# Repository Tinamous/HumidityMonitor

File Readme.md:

3D Printer Filament Humidity Controlled Storage
===============================================

Comprises of:

* Outer box (19L XL Really Useful Box).
* Laser cut acrylic silica gel case
* Particle Photon based humidity sensing and fan control PCB inside silica gel case.
* Self indicating silica gel inside #2.

1) Outer box
---------------------
A 19L XL A4 suspension folder Really Useful Box works well. Be sure to get the one with the high lid. (not the regular 19L box).

* Needed: Staples link to case.
* Maplin: http://www.maplin.co.uk/p/really-useful-19l-xl-box-n68fl (Untested but it's a lot cheaper than the staples one!)

The lid of the 19L XL case will need to be drilled to hold the acrylic silica gel cartridge in place. Do this before gluing the cartridge so the acrylic can be used as a template.

Place what is labeled as the top piece in the designs (actually the bottom piece with all the holes in it) onto the lid and mark/drill the 4 corner screws.

If you wish for the power to go in via the top (prevents boxes being stacked but is obvious that it is powered so prevents people missing it) use the large bottom piece (actually top) with the larger round hole in it and align the two corner screws then drill out the larger hole in the lid.

Power connectors were sourced from eBay (http://www.ebay.co.uk/itm/PLUGZ2GO-2-1MM-X-5-5MM-PANEL-MOUNT-DC-PLUG-SOCKET-JACK-CHOICE-OF-COLOUR-/221456273750?var=&hash=item338fd29156:m:m85llLg3q2OnjM6yf-dwyPw), be sure you can get the same before drilling the power connector hole in the lid. 

Alternativly power connection may be done from the side of the lid by running the power cable out of either top or bottom gel case holes, this would allow the boxes to be stacked, although it makes it less obvious theirs a cable connected so care needs to be taken.

M4 x 70mm machine screws with washer+wingnut on the lit are used to hold the actylic case to the lid. (See notes below on re-filling the silica gel)

2) Laser Cut Acrylic Gel Case
-----------------------------
5mm clear acrylic cut as detailed in Hardware\Case\LaserCut

(You can use another colour obviously but the clear is cheaper and allows the self indicating gel to be seen).

The case contains a 40mm fan. A standard 3 pin PC fan should be used with a filter to prevent silica gel getting in to it.

3) Humidity Monitor.
---------------------

Use Particle Photon (or can use Particle Core device).

See Hardware\PCB\V2

Don't use V1 as the FET has Source/Drain the wrong way around.

PCB available from OSHPark: https://oshpark.com/shared_projects/nOVDuNCE

JP3 or JP4 are used for the HTU21 sensor. SparkFun and eBay boards have swapped SDA/SCL, watch for correct version.
* JP3 is for the eBay version
* JP4 is for SparkFun version.

Build using build.particle.io, see source folder.

A 12V power supply us needed capable of supplying upto 500mA (depends on the fan).

If a 5V fan is used a 5V PSU can be used and the onboard regulator not fitted, instead connecting the Vin to VOut holes with a piece of wire.

The PCB is mounted to the case with 4x 10mm plastic standoffs and 8x M3x8mm bolts from either side.

4) Self indicating silica gel
-----------------------------
Almost any silica gel can be used and doesn't need to be self indicating but it helps with seeing when the gel needs to be dried and when drying the gel that it is ready.

Gel should be stored in a sealed box/bag when not in use.

Gel can be re-generated by heating in an electric (untested on gas) oven for about 3 hours at 110°C

5) Connection to Tinamous
-------------------------
Optional step. Tinamous supports Particle devices by use of the ParticleBot in Tinamous and will automatically bring in and store devices/measurements so the humidity can be remotely monitored.

PLA Filament storage 24 hour humdity chart:

PLA Filament storage 7 day humidity chart with change of gel:

Notes
=====

Replacing the silica gel.
--------------------------

This needs to be done regularly (depending on usage), ca. every month and the silica gel dried (110C 3hrs spread out on a baking tray). I typically replace when it gets to about 20% humidity in the box.

The silica gel can be dried and re-used.

Silica gel will try to go everywhere.

* Remove acrylic case from box lid (place on flat surface, undo wing nuts on top of box.
* Remove lid upwards leaving acrylic case on flat surface.
* Replace 2x win nuts onto acrylic case at PCB end to hold the large top piece in place
* Remove small top piece from top to expose silica gel
* Remove 2x screws that were holding the top peice in
** failure to remove these now will result in silica gel getting wedged behind them and stopping correct alignment.
* Pour gel into a container (suggest Sistem 2.35L tub - http://www.amazon.co.uk/gp/product/B005D6Y4IA?psc=1&redirect=true&ref_=oh_aui_detailpage_o03_s00)
* Put funnel into opening
* Slowly pour fresh silica gel into acrylic case, shaking to move the gel down the case as you go
* Do not fill completly full, allow 1/2-1 inch space when the case is closed up and stood tall 
* Re-Fit small lid peiece
* Holding top in place, stand case tall to allow silica gel to fully move down to the fan and make re-fitting screws easier.
* Refit 2x screws for the small lid piece.
* Stand back down, remove 2x wingnuts to allow lit to be fitted.
* Fit box lit and re-fit wing nuts.

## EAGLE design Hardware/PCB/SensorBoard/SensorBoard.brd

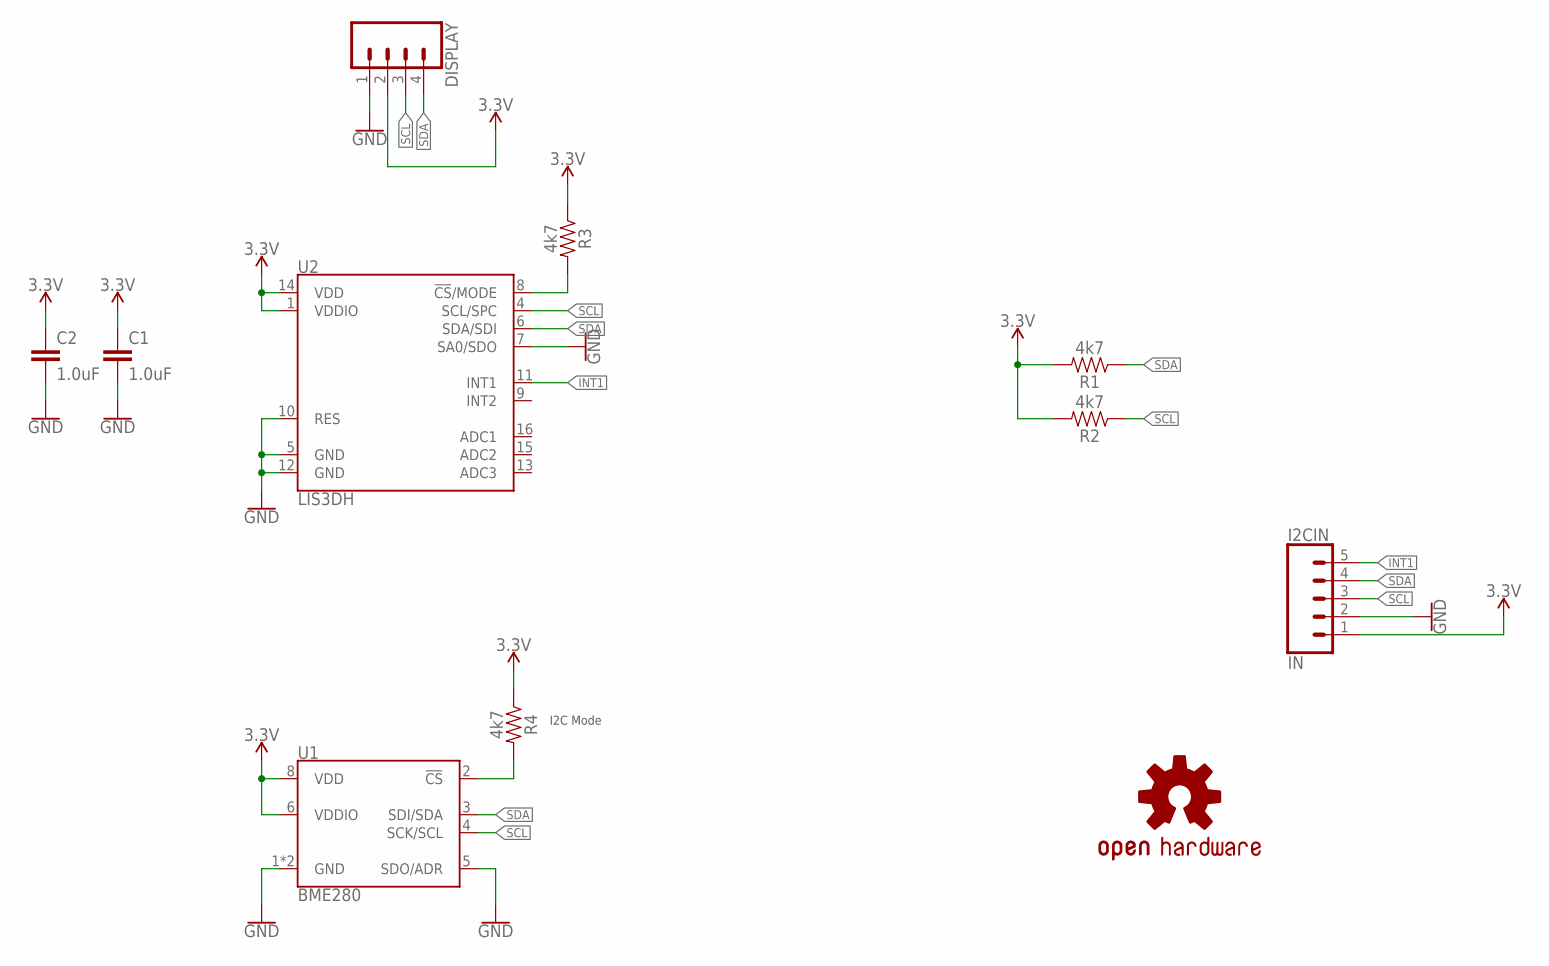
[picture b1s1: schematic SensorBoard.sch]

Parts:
C1, C2: 1.0uF; 0805
DISPLAY: CONN_04; 1X04
I2CIN: IN; 1X05
LOGO1: OSHW-LOGOL; OSHW-LOGO-L
R1, R2, R3, R4: 4k7; 0805
U1: BME280; LGA-8-2.5X2.5
U2: LIS3DH; LGA-16-3X3

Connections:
3.3V: C1.1, C2.1, DISPLAY.2, I2CIN.1, R1.2, R2.2, R3.1, R4.1, U1.6 (VDDIO), U1.8 (VDD), U2.1 (VDDIO), U2.14 (VDD)
GND: C1.2, C2.2, DISPLAY.1, I2CIN.2, U1.1 (GND), U1.5 (SDO/ADR), U1.7 (GND), U2.5 (GND), U2.7 (SA0/SDO), U2.10 (RES), U2.12 (GND)
INT1: I2CIN.5, U2.11 (INT1)
unnamed: R4.2, U1.2 (!CS)
unnamed: R3.2, U2.8 (!CS!/MODE)
SCL: DISPLAY.3, I2CIN.3, R2.1, U1.4 (SCK/SCL), U2.4 (SCL/SPC)
SDA: DISPLAY.4, I2CIN.4, R1.1, U1.3 (SDI/SDA), U2.6 (SDA/SDI)

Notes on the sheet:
I2C Mode

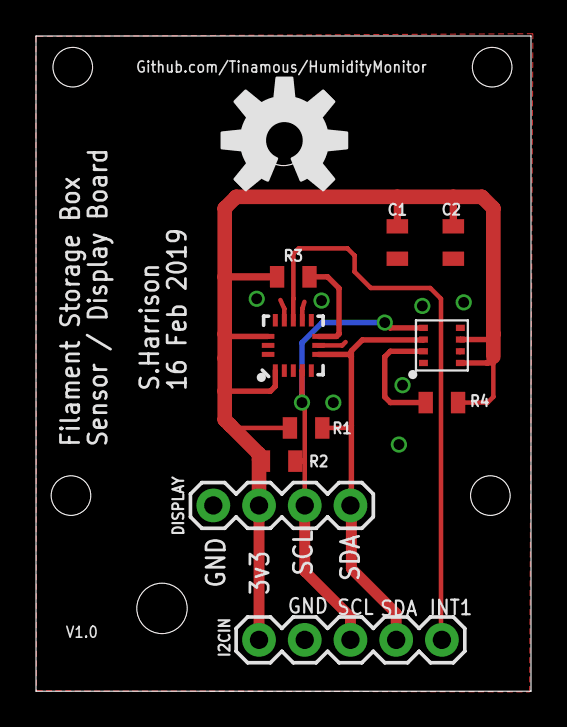
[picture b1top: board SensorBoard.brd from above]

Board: 2 copper layers, 27.5 x 36.4 mm, 11 parts (0 on the bottom side), 7 nets.

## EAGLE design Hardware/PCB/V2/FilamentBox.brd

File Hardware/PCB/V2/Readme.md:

Filament Box IoT Humidity Sense and Control
---------------------------------------------

Used to monitor the humidity level in a 3D filament storage box and re-circulate the air through a silica gel cartridge.

Notes:
* 7805 Regulator should be replaces with a switching "780x replacement" type device to keep heat down. The 7805 will get very hot dropping 12v to 5v.
* JP3 and 4 are variants of connectors for HTU21D breakout boards.
** JP4 should be used with the Spark Fun version (https://www.sparkfun.com/products/12064)
** JP3 should be used with the common eBay version (SDA/SCL swapped from Spark Fun version).
* Normal use is intended for 12V with a 12V fan. However if using a 5V fan the supply may be dropped to 5V and IC1 (7805) not fitted, instead pads 1 & 3 connected to feed 5V directly into the photo's 5V supply pin.
* Do not use photon USB B connector to provide 5V for fan, it will not supply the full 5v and may not have PCB traces strong enough for the fan current.

Untested at this time. Awaiting PCBs.

BOM:

All 0805 unless specified

F1 - Fuse Farnell 1822224

D1,D2 - IN4148W (2x)
D4 - MBRA140
D3 - Green Reverse LED
D7 - Red Reverse LED
D8 - Yellow Reverse LED

R1,R2 - 10k (2x)
R3 - 100k
R4 - 180R
R5,R6,R7 - 1k5 (3x)

Q1 - BC817
Q2 - NXP2301

C1 - 1.0uF 
C4 - 0.1 25V
C2,C5 - 0.1uF (x)

SG1 - Buzzer (Farnell: 2098836)

JP1 - 2 Pin Molex + Header + 2.1MM DC Jack 973-1148
JP2 - 3 Pin Moxel + 3 wire 40mm fan 9731156

IC1 - 7805 equivelant
JP3 - HTU21D equv
U3 - Photon (needs 2x 18Pin headers)

PCB Spacers (4x)
M3 Machine Screws (8x)

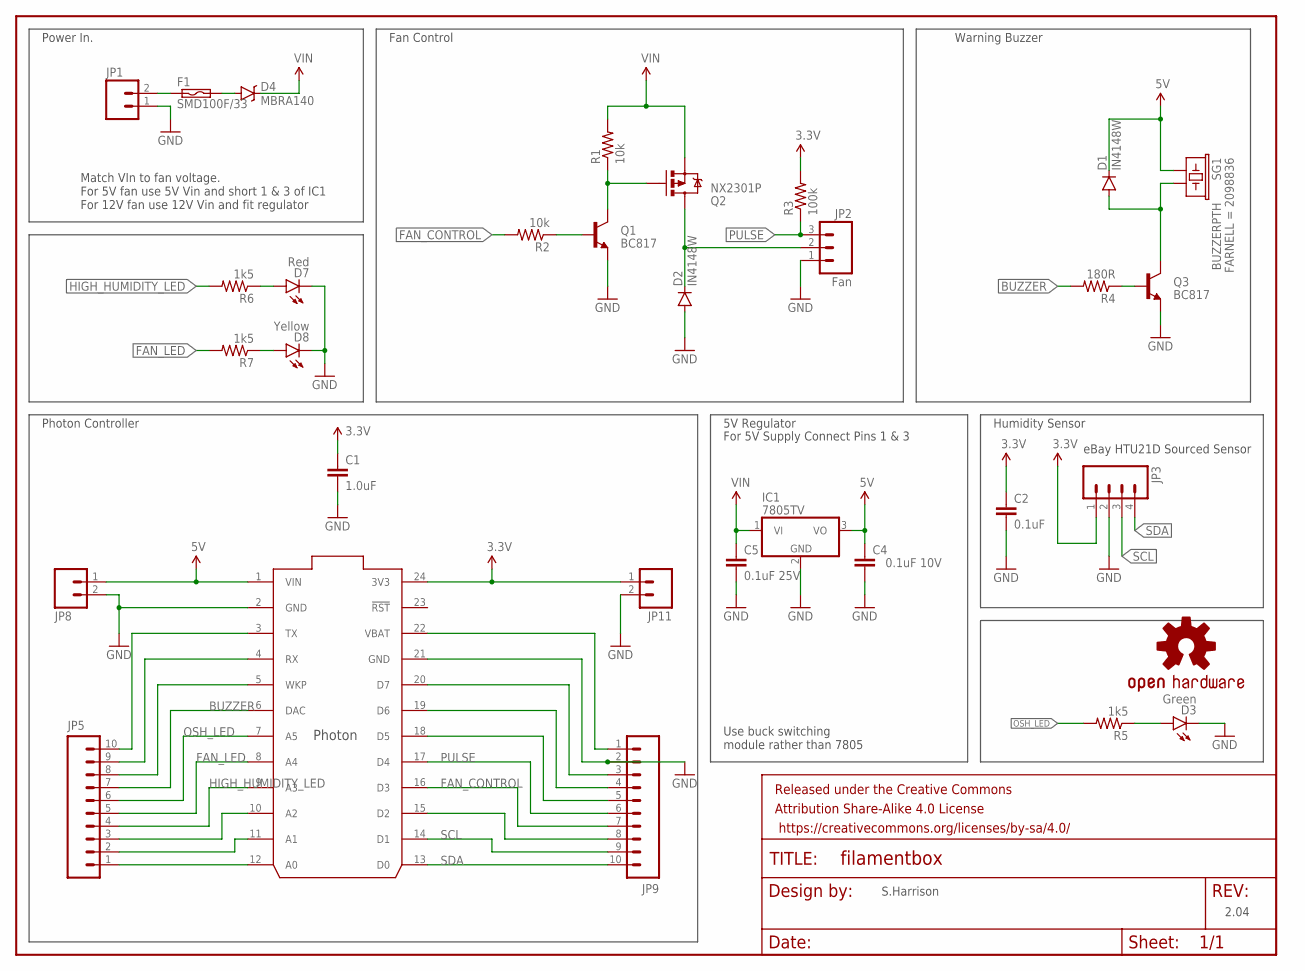
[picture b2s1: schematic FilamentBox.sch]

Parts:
C1: 1.0uF; 0805-CAP
C2: 0.1uF; 0805-CAP
C4: 0.1uF 10V; 0805-CAP
C5: 0.1uF 25V; 0805-CAP
D1, D2: IN4148W; SOD-123
D3: Green; LED-1206-BOTTOM
D4: MBRA140; SMA-DIODE
D7: Red; LED-1206-BOTTOM
D8: Yellow; LED-1206-BOTTOM
F1: SMD100F/33; SMD050F; MFGPART 2920L075DR; FARNELL 1822224
FRAME1: FRAME-LETTER; CREATIVE_COMMONS
IC1: 7805TV; TO220V
JP1: M02POLAR; MOLEX-1X2
JP2: Fan; MOLEX-1X3
JP3: M04PTH; 1X04
JP5, JP9: M10NO_SILK_PTH_FEMALE; 1X10_NO_SILK
JP8, JP11: M021X02_NO_SILK; 1X02_NO_SILK
LOGO1: OSHW-LOGOL; OSHW-LOGO-L
Q1, Q3: BC817; SOT23-BEC
Q2: NX2301P; SOT23-3
R1, R2: 10k; 0805
R3: 100k; 0805
R4: 180R; 0805
R5, R6, R7: 1k5; 0805
SG1: BUZZERPTH; BUZZER-12MM; FARNELL 2098836
U3: PHOTON

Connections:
3.3V: C1.1, C2.1, JP3.1, JP11.1, R3.2, U3.24 (3V3)
5V: C4.1, D1.C, IC1.3 (VO), JP8.1, SG1.+ (1), U3.1 (VIN)
BUZZER: JP5.7, R4.2, U3.6 (DAC)
FAN_CONTROL: JP9.7, R2.2, U3.16 (D3)
FAN_LED: JP5.5, R7.2, U3.8 (A4)
GND: C1.2, C2.2, C4.2, C5.2, D2.A, D3.C, D7.C, D8.C, IC1.2 (GND), JP1.1, JP2.1, JP3.2, JP8.2, JP9.2, JP11.2, Q1.E, Q3.E, U3.2 (GND), U3.21 (GND)
HIGH_HUMIDITY_LED: JP5.4, R6.2, U3.9 (A3)
unnamed: JP5.1, U3.12 (A0)
unnamed: Q1.C, Q2.1 (G), R1.1
unnamed: JP5.2, U3.11 (A1)
unnamed: Q1.B, R2.1
unnamed: JP5.3, U3.10 (A2)
unnamed: D2.C, JP2.2, Q2.3 (D)
unnamed: JP9.8, U3.15 (D2)
unnamed: JP5.8, U3.5 (WKP)
unnamed: JP5.9, U3.4 (RX)
unnamed: JP5.10, U3.3 (TX)
unnamed: Q3.B, R4.1
unnamed: D1.A, Q3.C, SG1.- (2)
unnamed: JP9.3, U3.20 (D7)
unnamed: JP9.1, U3.22 (VBAT)
unnamed: D3.A, R5.1
unnamed: F1.1, JP1.2
unnamed: D4.A, F1.2
unnamed: JP9.4, U3.19 (D6)
unnamed: JP9.5, U3.18 (D5)
unnamed: D7.A, R6.1
unnamed: D8.A, R7.1
OSH_LED: JP5.6, R5.2, U3.7 (A5)
PULSE: JP2.3, JP9.6, R3.1, U3.17 (D4)
SCL: JP3.3, JP9.9, U3.14 (D1)
SDA: JP3.4, JP9.10, U3.13 (D0)
VIN: C5.1, D4.C, IC1.1 (VI), Q2.2 (S), R1.2

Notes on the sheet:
5V Regulator
For 5V Supply Connect Pins 1 & 3
eBay HTU21D Sourced Sensor
Use buck switching module rather than 7805
Match VIn to fan voltage. For 5V fan use 5V Vin and short 1 & 3 of IC1 For 12V fan use 12V Vin and fit regulator
Power In.
Fan Control
Warning Buzzer
Photon Controller
Humidity Sensor
2.04
S.Harrison

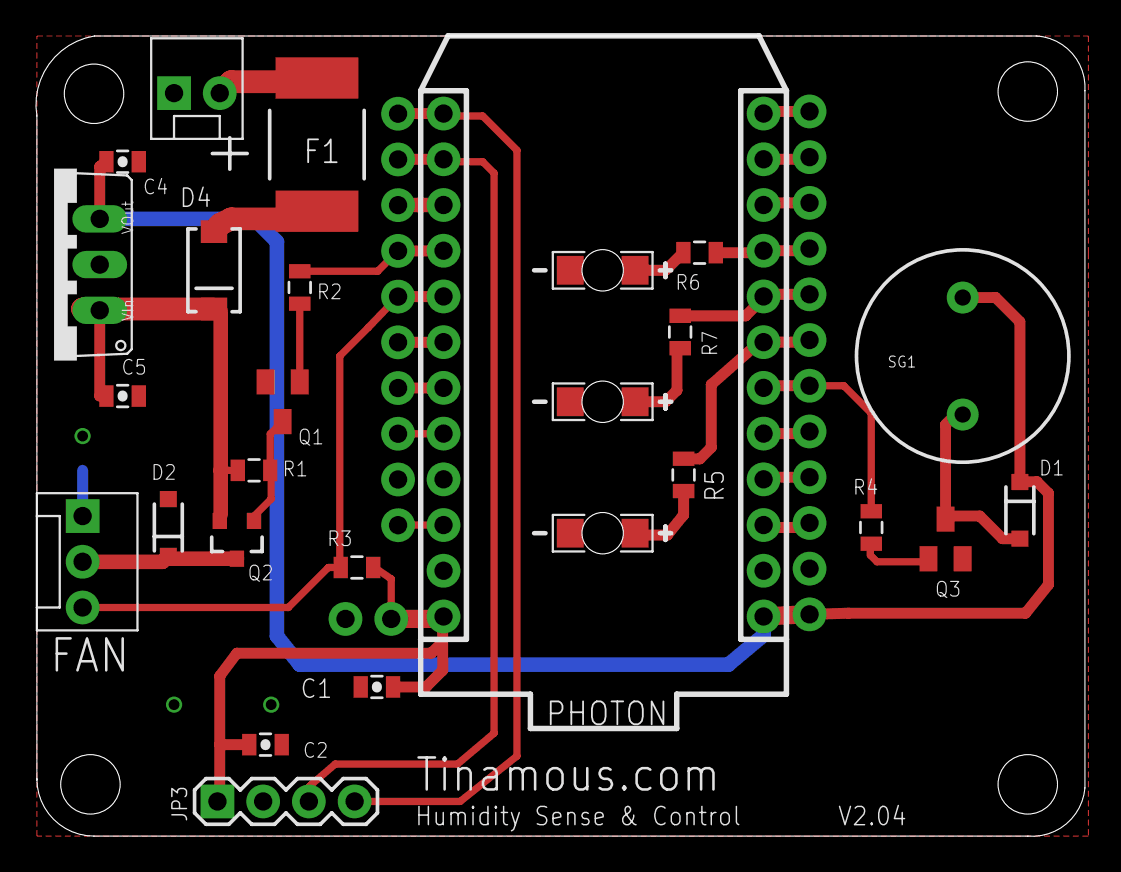
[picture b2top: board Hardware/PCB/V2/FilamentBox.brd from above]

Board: 2 copper layers, 58.3 x 44.5 mm, 37 parts (1 on the bottom side), 33 nets.

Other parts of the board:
U$1, U$2, U$3, U$4: STAND-OFF

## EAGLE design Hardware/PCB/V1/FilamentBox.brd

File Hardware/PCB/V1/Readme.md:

Version 1 Design.

Note that the Q1 has Source and Drain pins the wrong way around. When fitting Q1 rotate it 180 degrees and shift right so that the gate pin is not over a hole and on the right hand side.

Connect a wire between gate and the left most hole for Q1 (from above with the photon on the right). remaining 2 pins go into the remaining holes.

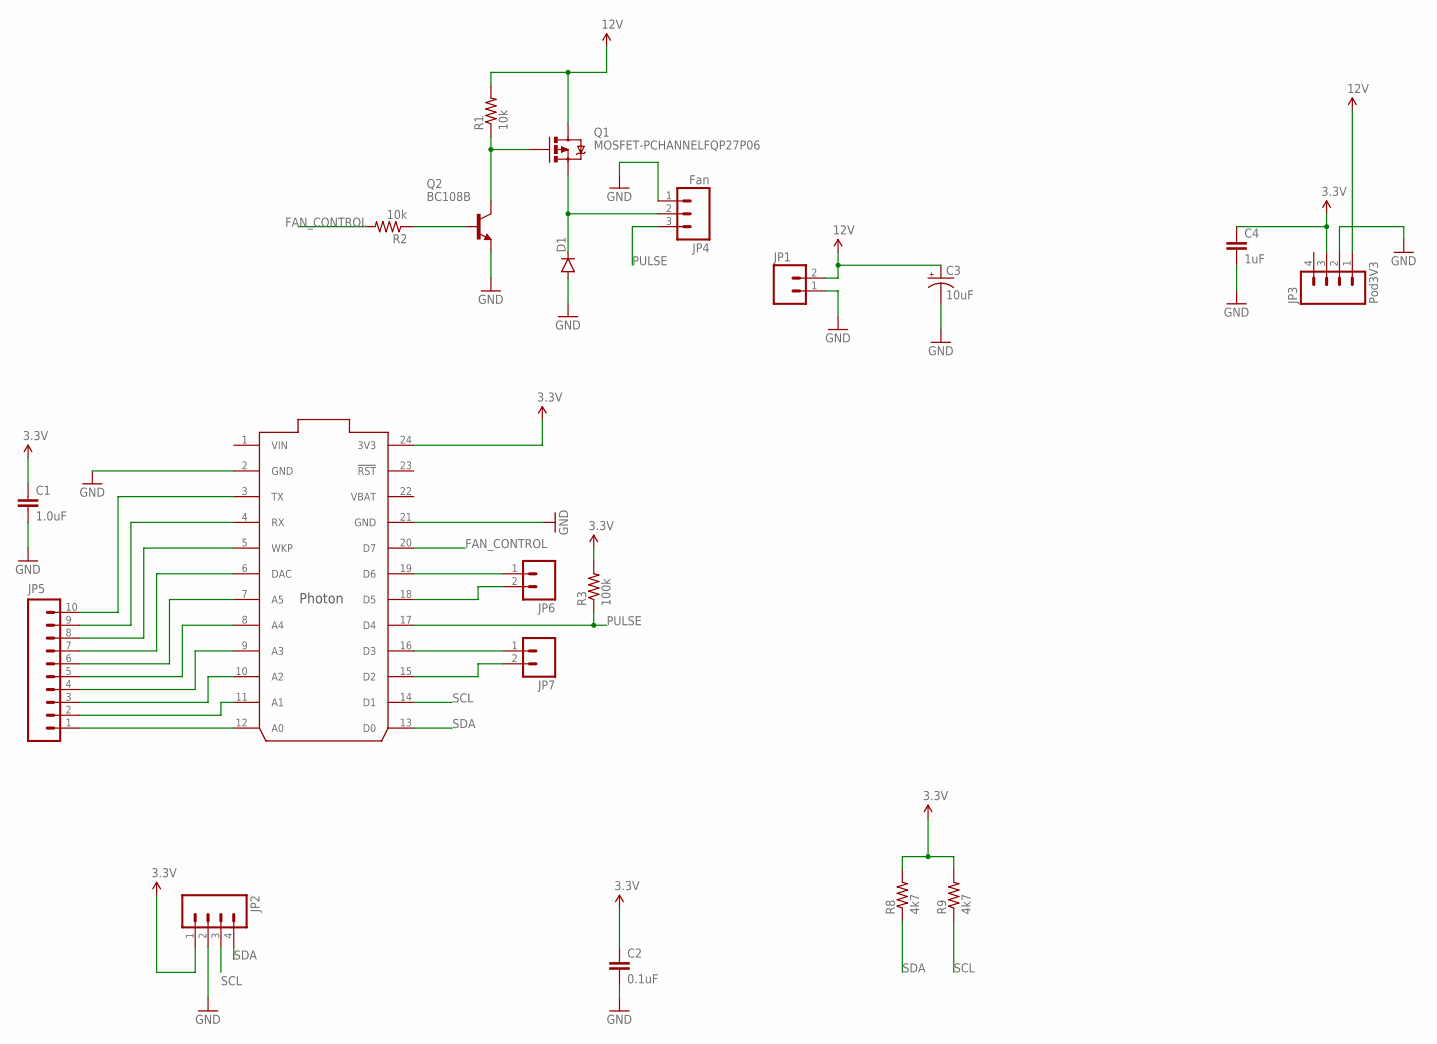
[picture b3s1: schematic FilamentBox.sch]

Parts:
C1: 1.0uF; 0805-CAP
C2: 0.1uF; 0805-CAP
C3: 10uF; CPOL-RADIAL-10UF-25V
C4: 1uF; 0805-CAP
D1: DIODESOD123; SOD-123
JP1: M02JST-PTH-2; JST-2-PTH
JP2: M04PTH; 1X04
JP3: Pod3V3; 1X04_NO_SILK_ALL_ROUND
JP4: Fan; MOLEX-1X3
JP5: M10NO_SILK_PTH_FEMALE; 1X10_NO_SILK
JP6, JP7: M021X02_NO_SILK; 1X02_NO_SILK
Q1: MOSFET-PCHANNELFQP27P06; TO220V
Q2: BC108B; TO18
R1, R2: 10k; 0805
R3: 100k; 0805
R8, R9: 4k7; 0805
U3: PHOTON

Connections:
3.3V: C1.1, C2.1, C4.1, JP2.1, JP3.3, R3.2, R8.2, R9.2, U3.24 (3V3)
12V: C3.1 (+), JP1.2, JP3.1, Q1.2 (D), R1.2
FAN_CONTROL: R2.2, U3.20 (D7)
GND: C1.2, C2.2, C3.2 (-), C4.2, D1.A, JP1.1, JP2.2, JP3.2, JP4.1, Q2.1 (E), U3.2 (GND), U3.21 (GND)
unnamed: JP5.1, U3.12 (A0)
unnamed: Q1.1 (G), Q2.3 (C), R1.1
unnamed: JP5.2, U3.11 (A1)
unnamed: Q2.2 (B), R2.1
unnamed: JP5.3, U3.10 (A2)
unnamed: D1.C, JP4.2, Q1.3 (S)
unnamed: JP5.4, U3.9 (A3)
unnamed: JP5.5, U3.8 (A4)
unnamed: JP5.6, U3.7 (A5)
unnamed: JP5.7, U3.6 (DAC)
unnamed: JP5.8, U3.5 (WKP)
unnamed: JP5.9, U3.4 (RX)
unnamed: JP5.10, U3.3 (TX)
unnamed: JP6.1, U3.19 (D6)
unnamed: JP6.2, U3.18 (D5)
unnamed: JP7.1, U3.16 (D3)
unnamed: JP7.2, U3.15 (D2)
PULSE: JP4.3, R3.1, U3.17 (D4)
SCL: JP2.3, R9.1, U3.14 (D1)
SDA: JP2.4, R8.1, U3.13 (D0)
VBAT: U3.22 (VBAT)
VIN: U3.1 (VIN)

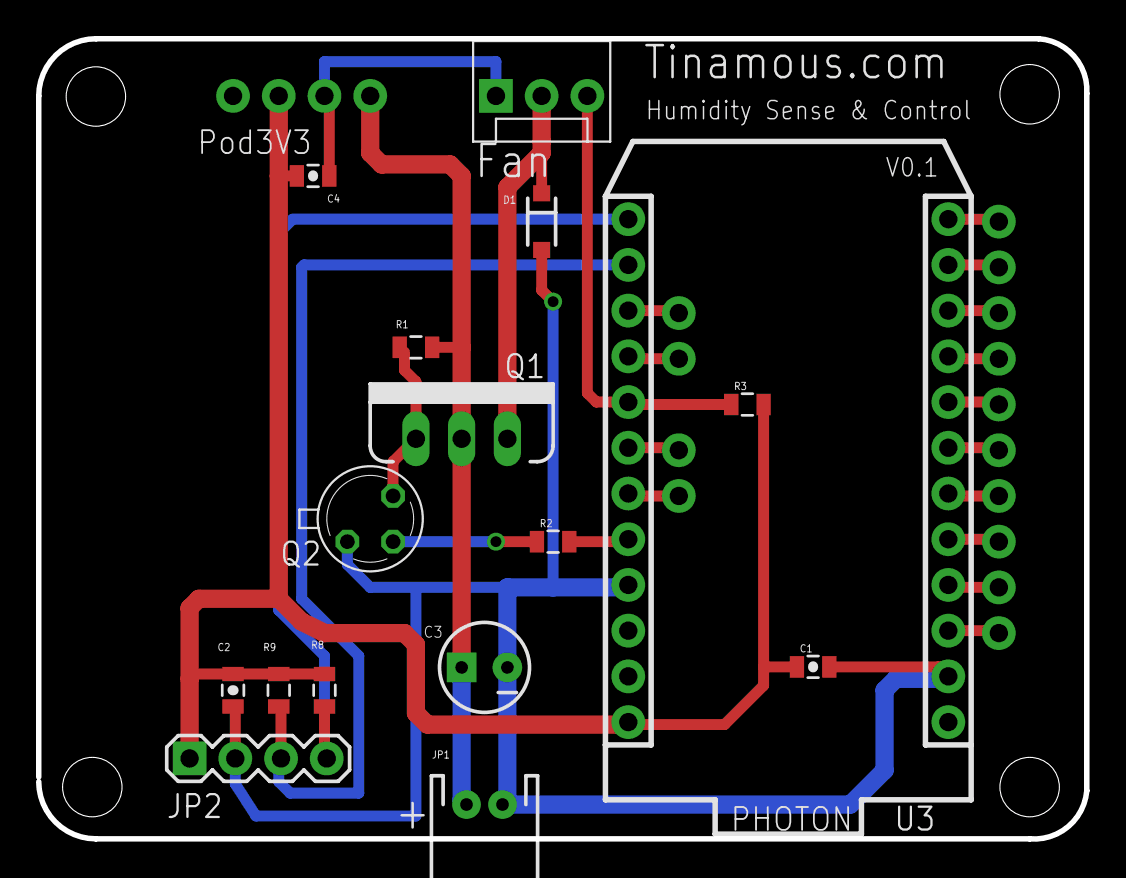
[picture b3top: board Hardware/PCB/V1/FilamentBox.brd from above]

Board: 2 copper layers, 58.2 x 44.5 mm, 24 parts (0 on the bottom side), 24 nets.

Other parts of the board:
U$1, U$2, U$3, U$4: STAND-OFF

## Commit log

2015-07-21 Initial commit of Particle Core/Photon powered Temperature and Humidity meter.
2015-07-22 Added comment about leaving sleep commented because of firmware bug
2015-08-05 Added latest 3D models, laser cutter design for partitiona and Photon based humidity monitor PCB
2015-08-05 Moved Particle Photon/Core code into Software folder.
2015-08-05 Updated with fan monitor and control.
    Increased loop delay to 15s so a measurement happens every 15s
2015-08-05 Made padding fixed 5mm width so that they print quicker and can be stacked to fill excess width allowing a better tollerance.
2016-02-03 Adding PCB files for V1 (0.1) and V2 (0.2) boards.
2016-02-03 Minor display update for PCB and added eagle project file.
2016-02-03 Updating main readme.
2016-02-03 Removed PCB files from Case folder.
2016-02-03 Removed unused 3D printed parts.
2016-02-03 Remove partition file as this is for a different design of case.
2016-02-03 Updated to latest laser cut acrylic plans.
2016-02-03 Added 3D printed funnel designs used to pour silica gel in.
2016-02-03 Updated source code to latest version to work with V2 (0.2) boards.
    Remopved lots of noisy publishing used during debug.
2016-02-03 Updated readme.
2016-02-03 Added instructions for replacing the silica gel and details on mounting holes.
2016-02-03 Added bill of materials.
2016-02-03 Tidied up markup.
2016-02-03 shortened title so it fits.
2016-02-03 Added Silica Gel to BOM (It's kind of important!) and price for PCB.
2016-02-03 Updated BOM
    Added cutting dxf for laser cutting the acrylic case.
2016-04-11 Added pictures.
2016-04-11 Added charts to show example of humidity control.
2017-01-03 Update (to 2.04)- Added reverse mount LEDs (Red, Yellow and Green for Humidity warning, fan status and OK (with OSH Logo)). Added poly fuse and diode for input protection. Swapped orientation of VIn 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
    Sent to DirtyPCBs (3-Jan-2017)
2017-01-03 Added Funnel3, an improved design for pouring silica gel into the acrylic case.
2017-01-03 Added files for the "mini" gel box - a self contained gel box - didn't work so well as it really needs air pushed through it
2017-03-15 Added media for V2.04 PCB and some assembly
2017-03-15 Added firmware for the V2.04 PCB
2018-06-07 Added part values
2018-06-07 Updated export images of PCB/Schematic
2018-06-26 Added PiHanle 3D printed handle.
2019-02-16 I2C Display adaptor and sensor board. Connects to I2C 4 pin connector on main board in place of HTU21D.
    Adds BME280, LIS3DH and I2C connector for 0.96" displays.
2019-02-16 Big handles for box to make opening the lid easier.
2019-02-16 0.96" Blue display holder and PCB mouont for main PCB.
2019-02-16 Added gitignore file to remove all the Eagle temp file noise.

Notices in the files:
parts and their libraries:
SparkFun-Capacitors: Licensing: Creative Commons ShareAlike 4.0 International - https://creativecommons.org/licenses/by-sa/4.0
SparkFun-Aesthetics: Released under the Creative Commons Attribution Share-Alike 4.0 License
SparkFun-Aesthetics: https://creativecommons.org/licenses/by-sa/4.0
